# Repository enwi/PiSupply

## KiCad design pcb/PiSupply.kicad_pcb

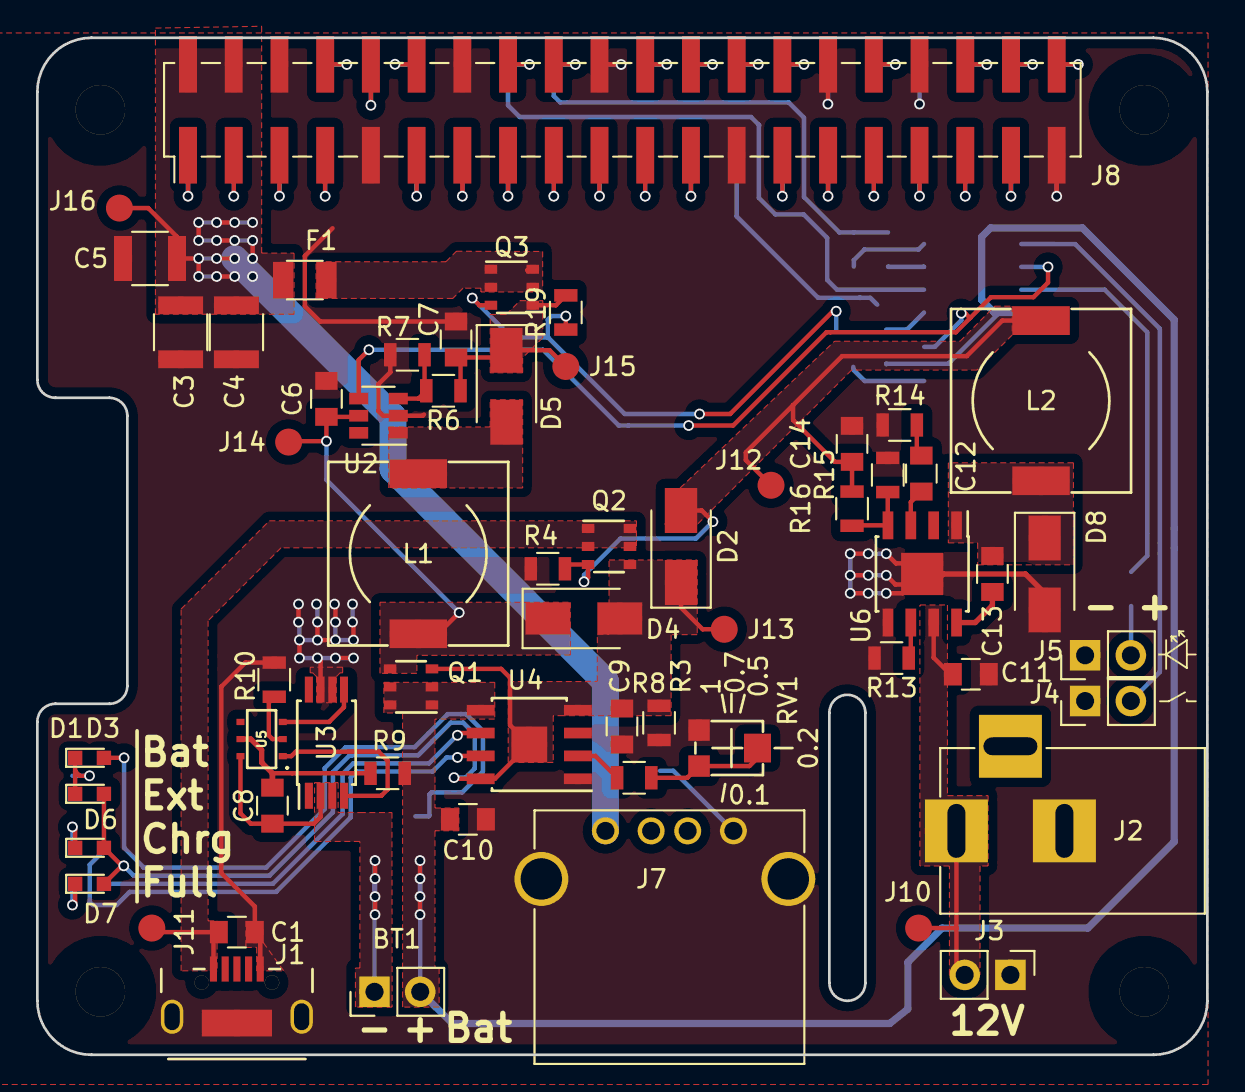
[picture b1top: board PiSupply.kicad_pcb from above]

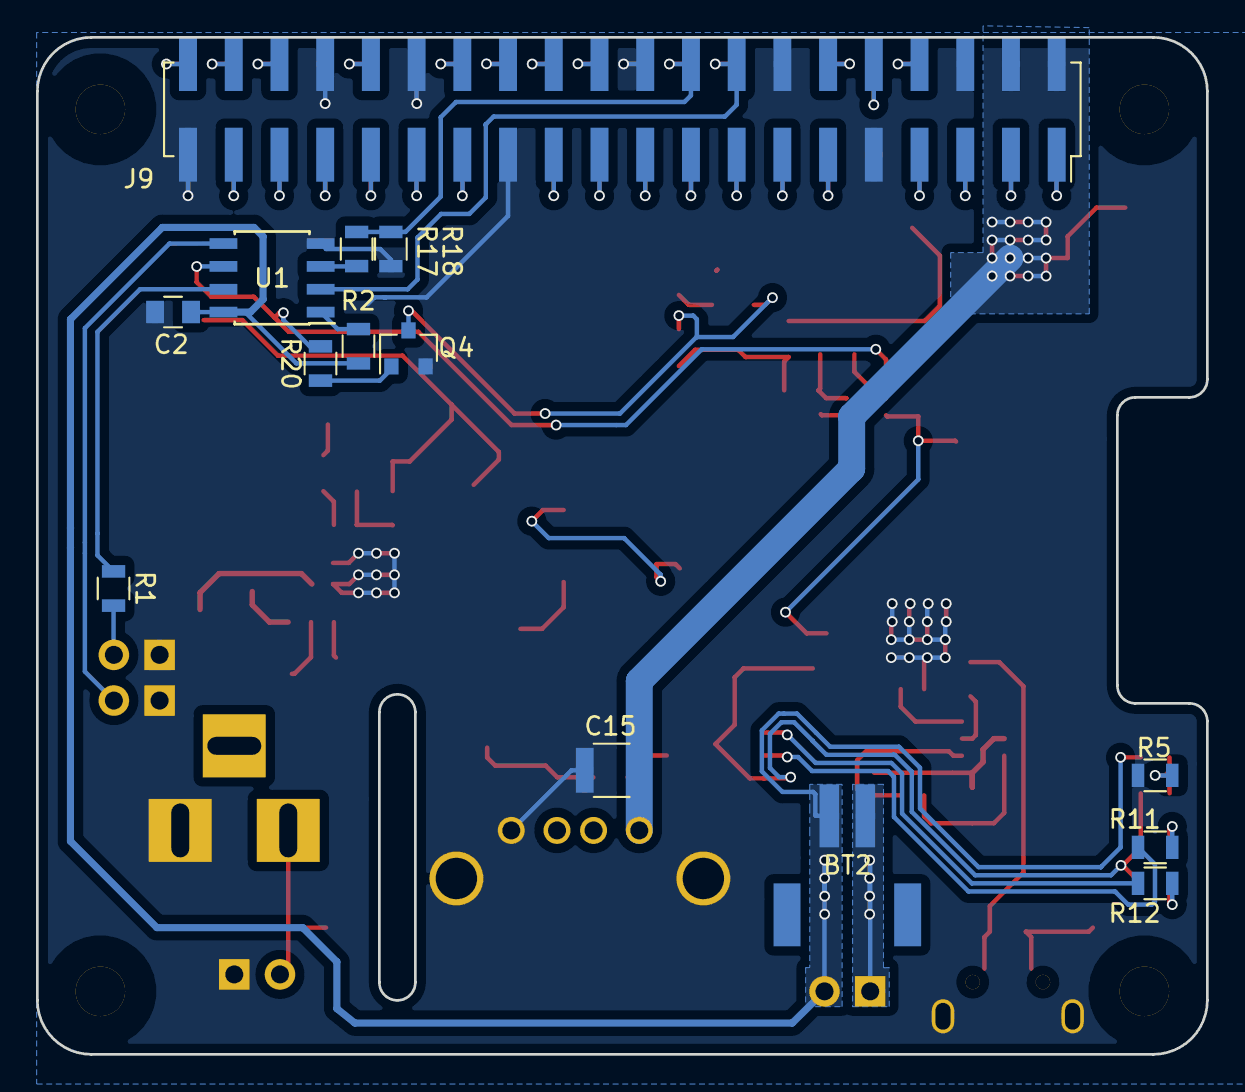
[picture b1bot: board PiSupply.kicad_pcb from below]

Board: 2 copper layers, 65.0 x 56.5 mm, 74 parts (14 on the bottom side), 68 nets.

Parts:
BT1: Battery_Cell_THT; Pin_Header_Straight_1x02_Pitch2.54mm
BT2: Battery_Cell_THT; conn_jst_2
C1, C2, C6, C7, C11: 10µF; C_0805
C3, C4, C5, C15: 100µF; C_1210
C8, C9, C10: 0.1µF; C_0805
C12: 150pF; C_0805
C13: 100nF; C_0805
C14: 22µF; C_0805
D1: LED Red; LED_0603
D2, D4, D5: SS34; D_SMA
D3, D7: LED Green; LED_0603
D6: LED Blue; LED_0603
D8: SS34 DO214AC 1N5822; D_SMA
F1: NANOSMD400LR-C-2; Fuse_SMD1206_Reflow
J1: USB_OTG; usb_micro_smd2
J2: Barrel_Jack; BARREL_JACK
J3, J4, J5: CONN_01X02; Socket_Strip_Straight_1x02_Pitch2.54mm
J7: USB_A
J8: Raspberry_Pi_2_3; Pin_Header_Straight_2x20_Pitch2.54mm_SMD
J9: Raspberry_Pi_2_3; Socket_Strip_Straight_2x20_Pitch2.54mm_SMD
J10, J11, J12, J13, J14, J15, J16: TEST_1P; Measurement_Point_Round-SMD-Pad_Small
L1: 4.7µH - CDRH104R; CDRH10RT_footprint
L2: 4.7µH; CDRH10RT_footprint
Q1, Q2, Q3: SI3443DDV; TSOP-6
Q4: Q_NPN_BEC; SOT-23
R1: 1k5; R_0805
R2, R3, R4, R18, R19: 10k; R_0805
R5, R10, R20: 1k; R_0805
R6: 47k; R_0805
R7: 6.2k; R_0805
R8: 1k2; R_0805
R9: 100; R_0805
R11, R12: 1.5k; R_0805
R13, R14: 100k; R_0805
R15: 40.2k; R_0805
R16: 221k; R_0805
R17: 5.6k; R_0805
RV1: 10 k pot TC33X-2-103E; Potentiometer_Trimmer_EIA_3mm
U1: ATTINY45-20SU; SOIC-8_3.9x4.9mm_Pitch1.27mm
U2: MT3608; SOT-23-6
U3: CEG8205A; TSSOP-8_4.4x3mm_Pitch0.65mm
U4: TP4056; SOIC-8_3.9x4.9mm_Pitch1.27mm
U5: DW01-P
U6: MP1584; SOIC-8-1EP_3.9x4.9mm_Pitch1.27mm

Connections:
5Vusb: C1.1, J1.1, J11.1, Q2.1, Q2.2, Q2.5, Q2.6
12Vin: C11.1, J2.1, J3.2, J10.1, U6.7
/Battery Charge + Protection/Vchrg: C9.1, D2.1, D3.2, D4.2, D6.2, D7.2, J13.1, Q1.3, Q2.4, R3.1, U4.4, U4.8
/Boost5V/5Vout: C7.1, D5.1, J15.1, Q3.4, R6.1, R19.2
/Boost5V/Vin: C6.1, D4.1, J14.1, L1.1, Q1.4, U2.5
/Buck5V/5Vout: C14.2, D2.2, J12.1, L2.2, Q2.3, R4.1, R16.1
B: J4.2, U1.5
Ctrl: R20.2, U1.6, U2.4
GND: C1.2, C2.2, C3.2, C4.2, C5.2, C6.2, C7.2, C9.2, C10.2, C11.2, C14.1, C15.2, D8.2, J1.5, J1.6, J2.2, J3.1, J4.1, J5.1, J7.4, J7.5, J8.6, J8.9, J8.14, J8.20, J8.25, J8.30, J8.34, J8.39, J9.6, J9.9, J9.14, J9.20, J9.25, J9.30, J9.34, J9.39, Q4.2, R3.2, R4.2, R5.2, R7.2, R10.1, R13.2, R14.2, R15.2, R18.1, RV1.1, U1.4, U2.2, U3.6, U3.7, U4.1, U4.3, U6.5, U6.9
LED: R1.2, U1.7
MCVcc: BT1.2, BT2.2, C2.1, C10.1, D1.2, Q1.1, Q1.2, Q1.5, Q1.6, R2.2, R9.2, U1.8, U4.5
unnamed: BT1.1, BT2.1, C8.2, U3.2, U3.3, U5.6
unnamed: C8.1, R9.1, U5.5
unnamed: C12.1, U6.3
unnamed: C12.2, R14.1
unnamed: C13.1, U6.8
unnamed: C13.2, D8.1, L2.1, U6.1
unnamed: D1.1, D3.1, R5.1
unnamed: D5.2, L1.2, U2.1
unnamed: D6.1, R11.1
unnamed: D7.1, R12.1
unnamed: F1.2, Q3.1, Q3.2, Q3.5, Q3.6
unnamed: J5.2, R1.1
unnamed: J8.1, J9.1
unnamed: J8.3, J9.3
unnamed: J8.5, J9.5
unnamed: J8.7, J9.7
unnamed: J8.8, J9.8
unnamed: J8.10, J9.10
unnamed: J8.11, J9.11
unnamed: J8.12, J9.12
unnamed: J8.13, J9.13
unnamed: J8.15, J9.15
unnamed: J8.17, J9.17
unnamed: J8.18, J9.18, R17.1, R18.2
unnamed: J8.19, J9.19
unnamed: J8.21, J9.21
unnamed: J8.22, J9.22
unnamed: J8.23, J9.23
unnamed: J8.24, J9.24
unnamed: J8.26, J9.26
unnamed: J8.27, J9.27
unnamed: J8.28, J9.28
unnamed: J8.29, J9.29
unnamed: J8.31, J9.31
unnamed: J8.32, J9.32
unnamed: J8.33, J9.33
unnamed: J8.35, J9.35
unnamed: J8.36, J9.36
unnamed: J8.37, J9.37
unnamed: J8.38, J9.38
unnamed: J8.40, J9.40
unnamed: Q3.3, Q4.3, R19.1
unnamed: Q4.1, R20.1
unnamed: R6.2, R7.1, U2.3
unnamed: R8.1, U4.2
unnamed: R8.2, RV1.2, RV1.3
unnamed: R10.2, U5.2
unnamed: R11.2, U4.7
unnamed: R12.2, U4.6
unnamed: R13.1, U6.6
unnamed: R15.1, R16.2, U6.4
unnamed: U3.4, U5.1
unnamed: U3.5, U5.3
PIctrl: R17.2, U1.3
PIon: J8.16, J9.16, U1.2
RST: R2.1, U1.1
Vout: C3.1, C4.1, C5.1, C15.1, F1.1, J7.1, J8.2, J8.4, J9.2, J9.4, J16.1

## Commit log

2020-04-01 Initial code commit
2021-10-07 Add PCB
